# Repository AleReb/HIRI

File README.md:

# HIRI
"Proyecto HIRI usa ESP32 C3 para recolectar datos ambientales con PMS5003ST y transmitirlos vía BLE. Los datos se guardan en una SD. NeoPixel muestra estados y la pantalla OLED es solo para depuración. Monitorea batería y entra en deep sleep si es necesario. Diseñado para proyectos IoT. se adjuntan el diseño del shield"
# Proyecto HIRI usando BLE - Versión 0.02

## Descripción
Este proyecto utiliza un **ESP32 C3** para recolectar datos de un sensor **Plantower PMS5003ST** y transmitirlos vía BLE. Además, incorpora una pantalla OLED para depuración y un NeoPixel para indicadores visuales. Los datos se guardan en una tarjeta SD en formato CSV para facilitar su análisis.

## Características principales

1. **Comunicación BLE**:
   - Recepción de datos de latitud y longitud desde una aplicación móvil vía BLE.
   - Envío de datos del sensor al dispositivo móvil conectado.

2. **Gestión de Datos**:
   - Almacenamiento en una tarjeta SD en formato CSV.
   - Identificación única de sesiones usando timestamps.

3. **Indicadores visuales**:
   - **NeoPixel** para estados BLE:
   - azul para el inicio.
   - violeta para error.
   - cambia de verde a rojo segun el material particulado (segun norma chilena siendo 50ppm el nivel peligroso).
   - parpadea 3 veces si esta desconetado.
   - cuando guarda en la micro sd se atenua la luz un poco.
     
   - **OLED** para mostrar información de depuración como voltaje de batería, estado BLE, y valores de los sensores.

4. **Gestión de batería**:
   - Monitoreo del voltaje de la batería.
   - Entrada en modo deep sleep si el voltaje es inferior al umbral.

5. **Gestión de versiones**:
   - Registro de cambios y versiones en el encabezado del código.

6. **Tabla de IDs predefinidos**:
   - Asociación de IDs de dispositivo con datos predefinidos.

## Requisitos

### Hardware
- **ESP32 C3**
- Sensor **Plantower PMS5003ST**
- Pantalla OLED con interfaz I2C
- NeoPixel
- Tarjeta SD y lector compatible
- Fuente de alimentación con monitoreo de voltaje

### Librerías
Incluye las siguientes librerías en tu entorno de desarrollo (Arduino IDE o equivalente usando la placa esp32 c3 dev con la version 2.0.17 de la gestion de placas):

- `Adafruit_NeoPixel`
- `esp_adc_cal`
- `SoftwareSerial`
- `Wire`
- `SPI`
- `SD`
- `U8g2lib`
- `TimeLib`
- `BLEDevice`

## Instalación

1. **Clonar el repositorio**:
   ```bash
   git clone https://github.com/tu-usuario/proyecto-hiri.git
   cd proyecto-hiri
   ```

2. **Configurar el entorno de desarrollo**:
   - Abre el archivo principal en tu IDE.
   - Configura los pines según tu hardware.

3. **Carga del código**:
   - Conecta el ESP32 C3 a tu computadora.
   - Carga el código al ESP32 C3 desde tu IDE.

## Uso

1. Conecta la fuente de alimentación al ESP32 C3.
2. Abre la aplicación móvil para interactuar con el dispositivo vía BLE.
3. Observa el estado de conexión y los datos en la pantalla OLED.
4. Los datos recolectados se guardarán automáticamente en la tarjeta SD.

## Contribuir

1. Realiza un fork del proyecto.
2. Crea una nueva rama para tu característica o corrección de error:
   ```bash
   git checkout -b nueva-caracteristica
   ```
3. Haz commit de tus cambios:
   ```bash
   git commit -m "Añadida nueva característica"
   ```
4. Envía tus cambios:
   ```bash
   git push origin nueva-caracteristica
   ```
5. Abre un Pull Request en el repositorio principal.

## Licencia
Este proyecto está licenciado bajo la Licencia MIT. Consulta el archivo `LICENSE` para más detalles.

## Contacto
Si tienes preguntas o sugerencias, no dudes en contactar a:
**Alejandro Rebolledo. arebolledo@udd.cl**

## Registro de Cambios

### Versión 0.02.1
- Ajustes en la lógica de guardado de datos.
- Implementación de recepción de datos BLE (latitud, longitud, etc.).
- Mejoras en los indicadores NeoPixel y mensajes OLED.

### TO DO
- Mejorar la gestion y registro de dispostivos.
- Mejorar la forma de guardar los datos en el csv.

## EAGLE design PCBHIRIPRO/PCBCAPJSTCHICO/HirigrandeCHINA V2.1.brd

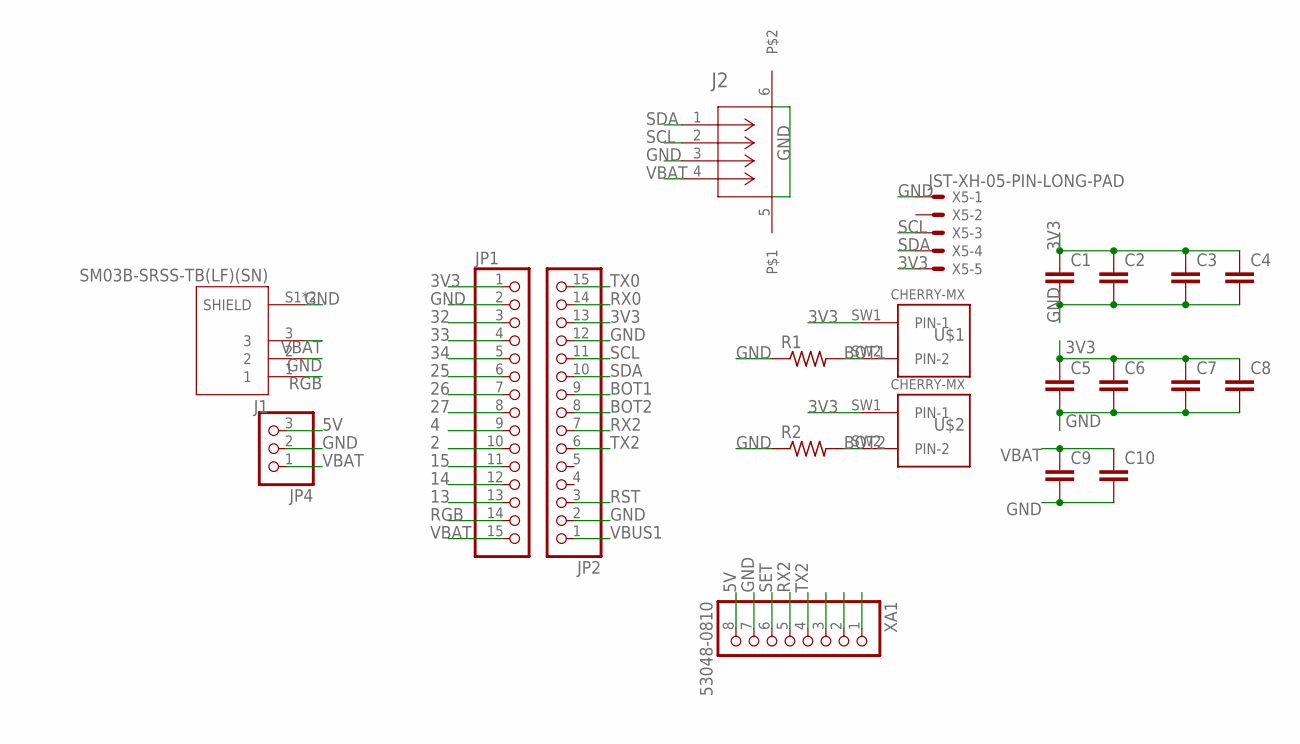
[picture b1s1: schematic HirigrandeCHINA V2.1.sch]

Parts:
C1, C2, C3, C4, C5, C6, C7, C8, C9, C10: C-EUC4532; C4532
J1: SM03B-SRSS-TB(LF)(SN); JST_SM03B-SRSS-TB(LF)(SN)
J2: SM04B-SRSS-TB; CONN_SM04B-SRSS-TB_JST
JP1, JP2: PINHD-1X15; 1X15
JP4: PINHD-1X3; 1X03
R1, R2: R-US_0204/7; 0204/7
U$1, U$2: CHERRY-MX
X5: JST-XH-05-PIN-LONG-PAD; JST-XH-05-PACKAGE-LONG-PAD
XA1: 53048-0810; MOLEX_53048-0810

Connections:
2: JP1.10
3V3: C1.1, C2.1, C3.1, C4.1, C5.1, C6.1, C7.1, C8.1, JP1.1, JP2.13, U$1.SW1 (PIN-1), U$2.SW1 (PIN-1), X5.5
4: JP1.9
5V: JP4.3, XA1.8
13: JP1.13
14: JP1.12
15: JP1.11
25: JP1.6
26: JP1.7
27: JP1.8
32: JP1.3
33: JP1.4
34: JP1.5
BOT1: JP2.9, R1.2, U$1.SW2 (PIN-2)
BOT2: JP2.8, R2.2, U$2.SW2 (PIN-2)
GND: C1.2, C2.2, C3.2, C4.2, C5.2, C6.2, C7.2, C8.2, C9.2, C10.2, J1.2, J1.S1 (SHIELD), J1.S2 (SHIELD), J2.3, J2.5, J2.6, JP1.2, JP2.2, JP2.12, JP4.2, R1.1, R2.1, X5.1, XA1.7
RGB: J1.1, JP1.14
RST: JP2.3
RX0: JP2.14
RX2: JP2.7, XA1.5
SCL: J2.2, JP2.11, X5.3
SDA: J2.1, JP2.10, X5.4
SET: XA1.6
TX0: JP2.15
TX2: JP2.6, XA1.4
VBAT: C9.1, C10.1, J1.3, J2.4, JP1.15, JP4.1
VBUS1: JP2.1

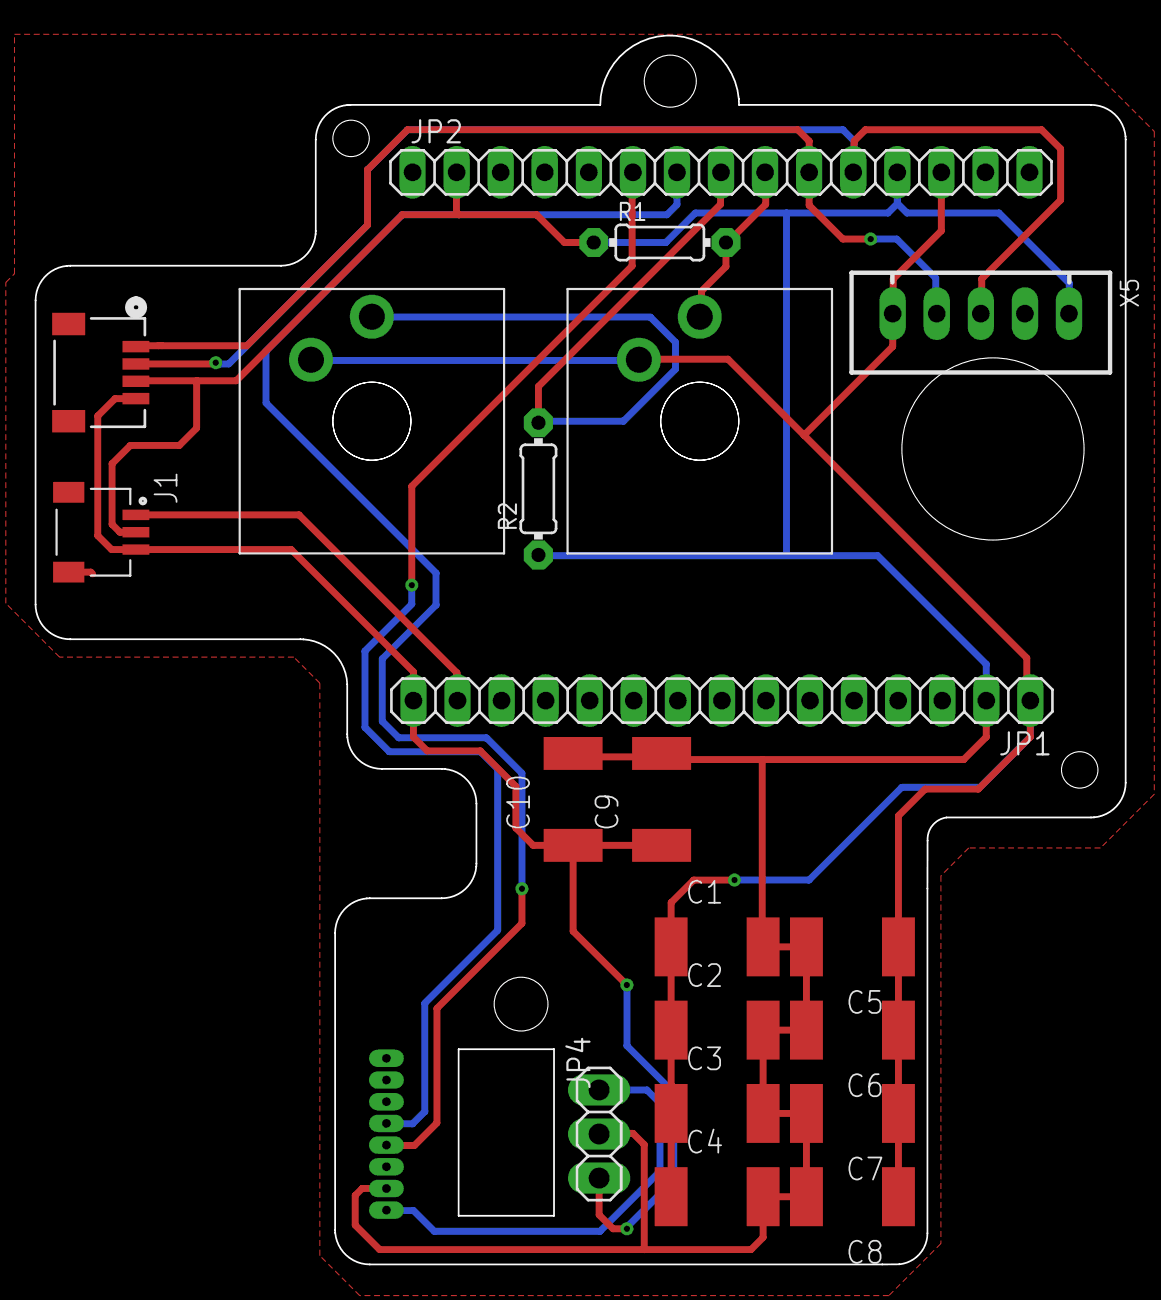
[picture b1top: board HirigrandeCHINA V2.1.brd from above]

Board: 2 copper layers, 62.8 x 70.8 mm, 21 parts (0 on the bottom side), 11 nets.

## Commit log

2025-01-22 se agrega el flutter echo por simon arias
    en un intento de seguir desarrollando la aps se hace la transferencia
2025-11-11 Add initial README with PCB information
2025-11-11 Rename PCBHIRIPRO/HirigrandeCHINA V2.1.brd to PCBHIRIPRO/PCBCAPJSTCHICO/HirigrandeCHINA V2.1.brd
    make folder
2025-11-11 Rename PCBHIRIPRO/HirigrandeCHINA V2.1.sch to PCBHIRIPRO/PCBCAPJSTCHICO/HirigrandeCHINA V2.1.sch
